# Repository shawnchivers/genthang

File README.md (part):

```
 ██████╗ ███████╗███╗   ██╗████████╗██╗  ██╗ █████╗ ███╗   ██╗ ██████╗ 
██╔════╝ ██╔════╝████╗  ██║╚══██╔══╝██║  ██║██╔══██╗████╗  ██║██╔════╝ 
██║  ███╗█████╗  ██╔██╗ ██║   ██║   ███████║███████║██╔██╗ ██║██║  ███╗
██║   ██║██╔══╝  ██║╚██╗██║   ██║   ██╔══██║██╔══██║██║╚██╗██║██║   ██║
╚██████╔╝███████╗██║ ╚████║   ██║   ██║  ██║██║  ██║██║ ╚████║╚██████╔╝
 ╚═════╝ ╚══════╝╚═╝  ╚═══╝   ╚═╝   ╚═╝  ╚═╝╚═╝  ╚═╝╚═╝  ╚═══╝ ╚═════╝ 
▀▀▀▀▀▀▀▀▀▀▀▀▀▀▀▀▀▀▀▀▀▀▀▀▀▀▀▀▀▀▀▀▀▀▀▀▀▀▀▀▀▀▀▀▀▀▀▀▀▀▀▀▀▀▀▀▀▀▀▀▀▀▀▀▀▀▀▀▀▀▀▀▀
      M E G A   D R I V E  /  G E N E S I S   ·   T A N G   N A N O   2 0 K
```

# Gen Thang

**Gen Thang is a DIY Sega Genesis / Mega Drive console project for the
[Sipeed Tang Nano 20K](https://wiki.sipeed.com/hardware/en/tang/Tang-Nano-20K/Nano-20K.html).**
A typical emulator recreates a console in software. Gen Thang does it in
hardware instead, using an FPGA chip configured to work like the original console.

Copy your own game ROMs to a microSD card (also called a TF card), choose a game
from the on-screen menu, and play. The standard build sends video and audio over
720p HDMI. You need a computer to program the board initially, but not to play.
Games are not included.

You can build it as a **TV console with Genesis controllers** or a **handheld
with built-in buttons and a small screen**. This repository contains the FPGA
design, menu firmware, build tools and optional PCB and printable-case designs.
You can use a [prebuilt release image](#choose-a-release-image) without compiling
the source yourself.

<p align="center">
  
</p>
<p align="center"><sub>Three-button handheld mock-up: Streets of Rage 2 frames from
Gen Thang's Verilator simulation composited onto a 3D render.
This is not footage from a physical handheld.
<a href="hardware/modern-3btn-handheld/index.html">Explore the handheld build guide.</a></sub></p>

> **Alpha software.** Gen Thang is under active development and is published as an
> early alpha. Expect bugs, game-compatibility gaps, missing features and breaking
> changes between releases. The default dual-DB9 build and raw-button variant are
> built and timing-checked but have not yet been tested on the new canonical wiring. The
> legacy single-DB9 breadboard image was tested by the author with a wired Genesis
> pad on its now-deprecated wiring, but only that one setup. Save
> states are experimental. Core switching rewrites the board's SPI flash. There is
> no warranty; you build, wire and flash at your own risk, and wiring mistakes can
> damage the board or a controller. See [Disclaimer](#disclaimer).

## Contents

**First build?** Start with [What you need](#what-you-need), then choose an
[assembly guide](#assembly-guides) for your controller or handheld arrangement.
The detailed pin tables and developer sections are references; you do not need
to read them all to understand the project.

- **See what it does:** [Features](#features) · [Game gallery](#game-gallery-streets-of-rage-2-sonic-2-and-x-men)
- **Build the hardware:** [Assembly guides](#assembly-guides) · [PCB and printable case](#pcb-and-printable-case) · [DB9 + biomech build guide](hardware/dual-db9-opt-pcb/index.html)
- **Set up the board:** [What you need](#what-you-need) · [Choose a release image](#choose-a-release-image) · [Flash](#1-flash-the-board) · [Prepare the card](#2-prepare-the-tf-card) · [Connect controllers](#3-connect-a-controller)
- **Play and use the menu:** [Using Gen Thang](#using-gen-thang) · [Controls](#controls) · [Options](#options-menu) · [Display options](#display-options) · [Save states](#save-states) · [USB upload](#uploading-roms-over-usb-serial) · [Core switching](#switching-cores)
- **Develop and debug:** [Build from source](#build-from-source) · [Simulation and screenshots](#simulation-and-screenshots) · [Limitations and troubleshooting](#limitations-and-troubleshooting)
- **About the project:** [Credits and tooling](#credits-and-tooling) · [Disclaimer](#disclaimer) · [License](#license)

## Features

- Motorola 68000 (fx68k), Z80 (T80), VDP, YM2612 (JT12) and SN76489 (JT89)
  implementations from the MiSTer Genesis core, running at 54 MHz and locked to
  the 60 Hz HDMI frame.
- 720p HDMI with audio. The picture is scaled to a centred 4:3 window.
- ROM browser on the TF card (`.md`, `.bin`, `.gen`, up to 4 MB) with an options
  page for resume, reset, save/load state and display settings.
- Controller options: two Genesis 3/6-button pads on DB9 breakouts (default), or
  twelve directly wired buttons for handhelds on the same physical GPIO layout.
- One save-state slot per game, with "Resume saved game" after a power cycle.
- Scanline and composite-blend display options.
- Optional ROM and core-image upload over the board's USB serial port (only in
  `GT_SERIAL_UPLOAD=1` builds; the default build leaves it out to fit the FPGA).

Not supported: SVP (Virtua Racing), EEPROM cartridges, Game Genie, interleaved
`.smd` ROMs and battery-backed cartridge saves (cartridge SRAM lives in SDRAM and is
only preserved inside a save state). Timing is fixed at NTSC / 60 Hz, as inherited
from MDTang.

## Game gallery: Streets of Rage 2, Sonic 2 and X-Men

Gen Thang's Genesis core playing the intro and attract mode (the unattended
demo) of three games, from ROMs you supply. These native 320x224 frames were
captured from Gen Thang running in its Verilator reference testbench (ideal memory;
see [Simulation and screenshots](#simulation-and-screenshots)). They are Gen Thang
simulation output, not captures from another emulator or from the physical HDMI port.

### Streets of Rage 2

<table>
  <tr>
    <td><br><sub>Boot logo</sub></td>
    <td><br><sub>Story intro</sub></td>
    <td><br><sub>The city</sub></td>
    <td><br><sub>Mr. X and the city</sub></td>
  </tr>
  <tr>
    <td><br><sub>Title screen</sub></td>
    <td><br><sub>Attract mode: Stage 1</sub></td>
    <td><br><sub>Attract mode: a fight</sub></td>
    <td><br><sub>High scores</sub></td>
  </tr>
</table>

### Sonic The Hedgehog 2

<table>
  <tr>
    <td><br><sub>Boot logo</sub></td>
    <td><br><sub>Title screen</sub></td>
    <td><br><sub>Chemical Plant Zone (demo)</sub></td>
  </tr>
  <tr>
    <td><br><sub>Chemical Plant Zone (demo)</sub></td>
    <td><br><sub>Aquatic Ruin Zone (demo)</sub></td>
    <td><br><sub>Aquatic Ruin Zone (demo)</sub></td>
  </tr>
</table>

### X-Men

<table>
  <tr>
    <td><br><sub>Boot logo</sub></td>
    <td><br><sub>Title screen</sub></td>
    <td><br><sub>Story text</sub></td>
    <td><br><sub>Demo: Cyclops</sub></td>
  </tr>
  <tr>
    <td><br><sub>Demo: Cyclops</sub></td>
    <td><br><sub>Demo: Cyclops</sub></td>
    <td><br><sub>Demo: Wolverine</sub></td>
    <td><br><sub>Demo: Wolverine</sub></td>
  </tr>
</table>

<sub>Frames produced by Gen Thang running in its Verilator reference testbench.
That testbench uses ideal memory and BRAM VRAM rather than the full board's SDRAM
controller and menu firmware; these are simulation captures, not physical HDMI
captures.</sub>

## Assembly guides

Start here for step-by-step hardware builds, including parts, printing, assembly
and firmware setup. Choose the guide and firmware that match your hardware.

| Build | Assembly guide | Firmware |
|---|---|---|
| Two-player DB9 console with biomechanical case | [Illustrated build guide](https://shawnchivers.github.io/genthang/hardware/dual-db9-opt-pcb/) · [Offline page](hardware/dual-db9-opt-pcb/index.html) | `db9` |
| Standalone L3 dual-DB9 carrier with stereo line-out | [Colorful build guide and capacitor chooser](https://shawnchivers.github.io/genthang/hardware/dual-db9-lineout-pcb/) · [Offline page](hardware/dual-db9-lineout-pcb/index.html) | [Official v1.9.3 DB9 image](https://github.com/shawnchivers/genthang/releases/download/v1.9.3/genthang_nano20k_db9_flash.bin) |
| GenThang Modern 3-button handheld (beta) | [Illustrated build guide](https://shawnchivers.github.io/genthang/hardware/modern-3btn-handheld/) · [Offline page](hardware/modern-3btn-handheld/index.html) | `raw` |

**DB9 bench references:** [O1 soldering and pre-power checks](hardware/dual-db9-opt-pcb/ASSEMBLY.md)
· [Biomechanical case printing and assembly](hardware/dual-db9-biomech-case/README.md)
· [L3 line-out assembly](hardware/dual-db9-lineout-pcb/ASSEMBLY.md)
· [L3 capacitor selection](hardware/dual-db9-lineout-pcb/index.html#caps).

## PCB and printable case

The [hardware directory](hardware/README.md) includes the
[O1 dual-DB9 carrier PCB](hardware/dual-db9-opt-pcb/README.md) for two Genesis
controllers and an original
[Giger-inspired biomechanical case](hardware/dual-db9-biomech-case/README.md)
for the carrier and Tang Nano 20K.

**Build the console:** the [DB9 + biomech assembly guide](https://shawnchivers.github.io/genthang/hardware/dual-db9-opt-pcb/)
([local page](hardware/dual-db9-opt-pcb/index.html)) walks through parts sourcing,
printing, soldering, continuity tests, flashing, two-player bring-up and fitting
the carrier into the biomechanical case. It includes CAD illustrations, direct
PCB/STL downloads and a printable bench copy. This O1 build uses HDMI audio, not
the separate line-out carrier.

- **PCB:** KiCad sources, fabrication ZIPs, BOM, assembly instructions and
  continuity-test tables.
- **Case:** printable [base STL](hardware/dual-db9-biomech-case/stl/case_base.stl)
  and [lid STL](hardware/dual-db9-biomech-case/stl/case_lid.stl), an editable
  [STEP model](hardware/dual-db9-biomech-case/dual-db9-biomech-case.step), and
  parametric CadQuery source. The case has been printed.

**Handheld (beta):** the [GenThang Modern 3-button build guide](https://shawnchivers.github.io/genthang/hardware/modern-3btn-handheld/)
([source](hardware/modern-3btn-handheld/index.html)) walks through printing and assembling a battery-powered A·B·C handheld
with a 3.5" IPS screen, with 3D renders, an interactive viewer, wiring diagrams and the three
[STLs](hardware/modern-3btn-handheld/stl/). It uses the `raw` firmware.

**Standalone stereo line-out:** the [L3 carrier](hardware/dual-db9-lineout-pcb/README.md)
adds a 3.5 mm output for powered speakers, with GPIO31 left and GPIO17 right.
Its [colorful build guide](https://shawnchivers.github.io/genthang/hardware/dual-db9-lineout-pcb/)
includes a simple capacitor chooser, soldering and electrical
checks. The author confirms the GPIO17 audio move works and has submitted L3 to
OSH Park. Use the [L3 order ZIP](hardware/dual-db9-lineout-pcb/dual-db9-lineout-L3-OSHPARK.zip)
and the [official v1.9.3 DB9 image](https://github.com/shawnchivers/genthang/releases/download/v1.9.3/genthang_nano20k_db9_flash.bin).
L3 is a separate carrier; it does not fit the O1 biomechanical case above.

**OSH Park is the recommended PCB manufacturer for people within the USA.** Use the [OSH Park order ZIP](hardware/dual-db9-opt-pcb/dual-db9-opt-O1-OSHPARK.zip).

The carrier uses the standard `db9` firmware and the pinout in
[step 3](#3-connect-a-controller). It is unprotected **3.3 V-only**. This worked
on my personal configuration, but not all third-party controllers might work; only
3-button and 6-button SEGA OEM controllers were tested.

## What you need

- Tang Nano 20K and a USB-C cable.
- microSD / TF card (FAT32 or exFAT) and your own Mega Drive ROM files.
- HDMI display (with audio, if you want sound).
- A controller arrangement from [step 3](#3-connect-a-controller).
- Gowin Programmer (part of Gowin EDA) to write the flash. The Education edition
  1.9.11.03 is what was used for the releases.

ROM images and other copyrighted game data are **not** included.

## Choose a release image

Each release contains a bitstream for every controller arrangement. Every
`*_flash.bin` is a complete SPI-flash image (bitstream at `0x000000`, menu
firmware at `0x500000`); the `.fs` files are bitstream-only.

| Image | Controllers | Notes |
|---|---|---|
| `genthang_nano20k_db9_flash.bin` | Two Genesis pads on DB9 breakouts (default) | Canonical J6/J5 wiring, 3.3 V only; see [dual Genesis pads](#dual-genesis-pads-db9-build) |
| `genthang_nano20k_raw_flash.bin` | Twelve direct buttons | Handheld pinout, plus the Nano's speaker and a headphone jack; see [direct buttons](#direct-buttons-raw-build) |
| `genthang_nano20k_raw_3btn_flash.bin` | Single-player three-button handheld | Raw pinout; port 2 reads as unplugged and **Mode** alone opens the menu |
| `genthang_nano20k_db9_800x480_flash.bin`, `genthang_nano20k_raw_800x480_flash.bin` | Same pads, for an 800x480 TFT on a TFP401 board | Native 800x480 DVI, no HDMI audio; see [display options](#display-options) |

The wiring must match the image you flash. A mismatched image reads the wrong pins.

## Setup

### 1. Flash the board

Write the `*_flash.bin` for your controller arrangement at SPI-flash address
`0x000000`. Verify it against the release's `SHA256SUMS` first
(`sha256sum -c SHA256SUMS --ignore-missing`).

**Gowin Programmer GUI (Windows or Linux):** connect the board, open *Gowin
Programmer*, choose series **GW2AR** and device **GW2AR-18C**, then double-click the
operation. Set *Access Mode* to **External Flash Mode** and *Operation* to **exFlash
Erase, Program thru GAO-bridge**, pick the `*_flash.bin` file (switch the file
filter to `*.*`), set *Start Address* to `0x000000` and run it. The
[SNESTang installation guide](https://github.com/nand2mario/snestang/blob/main/doc/installation.md)
has screenshots of the same dialogs.

**Linux, command line:** the on-board BL616 debugger claims the FTDI interface;
release it first (repeat after every replug), then use the programmer. In our
testing openFPGALoader did not work with this board's debugger.

```sh
echo -n 1-2:1.0 | sudo tee /sys/bus/usb/drivers/ftdi_sio/unbind   # adjust 1-2 to your USB port
cd "$GOWIN_HOME/Programmer/bin"      # your Gowin EDA install directory
QT_QPA_PLATFORM=minimal ./programmer_cli --device GW2AR-18C --run 39 \
    --mcuFile /path/to/genthang_nano20k_db9_flash.bin --spiaddr 0x000000
```

A `.fs` file can be loaded into SRAM for a quick test, but it does not include the
menu firmware, so a flash image is required for normal use.

### 2. Prepare the TF card

Format the card with an MBR partition table and a FAT32 (or exFAT) filesystem, then
copy your `.md`, `.bin` or `.gen` ROMs onto it, in folders if you like. On Linux:

```sh
sudo parted /dev/sdX --script mklabel msdos mkpart primary fat32 1MiB 100%
sudo mkfs.vfat -F 32 -n GENTHANG /dev/sdX1
```

(Replace `/dev/sdX` with your card and double-check it first: this erases the card.)
Insert the card, connect HDMI and a controller, then power the board. To add ROMs
later, copy them to the card in a normal card reader. (Builds made with
`GT_SERIAL_UPLOAD=1` can also copy them over USB; see
[Uploading ROMs over USB serial](#uploading-roms-over-usb-serial).)

### 3. Connect a controller

Always **power the board off before wiring** controllers. The FPGA pins are 3.3 V
only and are not 5 V tolerant. In the tables below, the "FPGA pin" is the GPIO
number used in the constraints file; the "Nano contact" is the header position,
counted 1-20 from the USB-C end with the board viewed from above (USB at the top):
**J6** is the left header and **J5** the right header.

The original single-DB9 breadboard layout is documented separately in
[deprecated controller pinouts](docs/deprecated-pinouts.md). It is not included
in current releases.

#### Dual Genesis pads (`db9` build)

For a PCB instead of hand wiring, see the
[dual-DB9 carrier and matching printable case](#pcb-and-printable-case).

For two wired 3- or 6-button Genesis pads, use
`genthang_nano20k_db9_flash.bin`. Player 1 is entirely on J6 and player 2 entirely on J5.
Leave the Nano LCD connector and speaker header empty. Both ports use 3.3 V with
internal pull-ups; the DB9 pin 5 supply is 3.3 V.

| DB9 pin (male) | Signal | Player 1 FPGA pin (contact) | Player 2 FPGA pin (contact) |
|---|---|---|---|
| 1 | Up / D0 | 73 (J6.1) | 42 (J5.5) |
| 2 | Down / D1 | 74 (J6.2) | 41 (J5.6) |
| 3 | Left / D2 | 77 (J6.5) | 51 (J5.9) |
| 4 | Right / D3 | 27 (J6.8) | 48 (J5.10) |
| 5 | Pad supply | **3.3 V, not 5 V** (J6.19) | **3.3 V, not 5 V** (J5.16) |
| 6 | TL (B / A) | 28 (J6.9) | 49 (J5.12) |
| 7 | TH select (output) | 29 (J6.12) | 72 (J5.17) |
| 8 | Ground | GND (J6.20) | GND (J5.15) |
| 9 | TR (C / Start) | 30 (J6.13) | 71 (J5.18) |

##### P1 breadboard wiring

P1 can be built on a 30-row breadboard using only J6. Seat the Nano
component-side up with USB-C at the top, put J6.1 in hole `b5`, and connect a
passive **male DB9 screw-terminal or solder-cup breakout** with nine jumpers:

| DB9 pin | Function | Breakout jumper | Nano hole | Nano contact |
|---:|---|---|---|---|
| 1 | Up / D0 | terminal 1 to `a5` | `b5` | J6.1, GPIO73 |
| 2 | Down / D1 | terminal 2 to `a6` | `b6` | J6.2, GPIO74 |
| 3 | Left / D2 | terminal 3 to `a9` | `b9` | J6.5, GPIO77 |
| 4 | Right / D3 | terminal 4 to `a12` | `b12` | J6.8, GPIO27 |
| 5 | Controller supply | terminal 5 to `a23` | `b23` | J6.19, **3.3 V only** |
| 6 | TL / B, A | terminal 6 to `a13` | `b13` | J6.9, GPIO28 |
| 7 | TH select | terminal 7 to `a16` | `b16` | J6.12, GPIO29 |
| 8 | Ground | terminal 8 to `a24` | `b24` | J6.20, GND |
| 9 | TR / C, Start | terminal 9 to `a17` | `b17` | J6.13, GPIO30 |

A bare DB9 does not fit a 2.54 mm breadboard. Check the numbered terminals and
your breadboard's internal row connections with a continuity meter before
connecting the Nano. DB9 pin 5 is **3.3 V only, never 5 V**; power off before
wiring or connecting a controller, and do not hot-plug this unprotected setup.
An optional 100 nF ceramic capacitor may be fitted directly across DB9 pins 5
and 8. Use the normal `genthang_nano20k_db9_flash.bin`; P2 may remain
disconnected.

Build it with:

```sh
GT_PAD=db9 ./build.sh
```

#### Direct buttons (`raw` build)

For handheld builds: twelve buttons, each switching an FPGA pin to GND (the
internal pull-ups are enabled), plus the Nano's speaker and a headphone jack (see
[speaker and headphone jack](#speaker-and-headphone-jack-raw-build)).

The pinout is laid out for a Nano mounted component side forward with USB-C at the
top. The left header (J6) faces the D-pad and the jack, and the right header (J5)
faces the face buttons. Groups sit on neighbouring pins, for neat solder runs or
multi-pin Dupont housings.

| Header pin | FPGA pin | Function | | Header pin | FPGA pin | Function |
|---|---|---|---|---|---|---|
| J6.8 | 27 | Up | | J5.3 | 76 | Start |
| J6.9 | 28 | Down | | J5.5 | 42 | X |
| J6.10 | 25 | Left | | J5.6 | 41 | A |
| J6.11 | 26 | Right | | J5.10 | 48 | Y |
| J6.12 | 29 | Headphone detect | | J5.12 | 49 | B |
| J6.13 | 30 | Jack R | | J5.13 | 86 | Mode |
| J6.14 | 31 | Jack L | | J5.17 | 72 | Z |
| J6.20 | GND | Button and jack ground | | J5.18 | 71 | C |
| | | | | J5.15 | GND | Button ground |

- Each face-button column shares neighbouring pins: X/A on J5.5–6, Y/B on
  J5.10/12 and Z/C on J5.17–18.
- The pins skipped on J5 belong to the TF card (80), the speaker amplifier (51,
  54–56) and the LED strip (79).
- Spare: 73, 74, 75 and 77 (J6.1, J6.2, J6.3, J6.5).
- In vector order, `btn_n[0..11]` (`B, A, Mode, Start, Up, Down, Left, Right, C, Y,
  X, Z`) uses pins `49, 41, 86, 76, 27, 28, 25, 26, 71, 48, 42, 72`.
- Releases up to 1.6.2 used the DB9 data pins for the raw build instead
  (`73, 74, 77, 27, 28, 30, 42, 41, 51, 48, 49, 71`). Rewire older raw builds when
  updating.

## Using Gen Thang

At power-on the menu lists the card's folders and ROMs sorted by name. If the card
cannot be read the status line says why (no reply, not initialised, not FAT32 /
exFAT). Picking a ROM streams it into SDRAM (about 7 s for 2 MB) and starts the game.

<p align="center"><sub>Menu overlay rendered by the Verilator testbench (see
<a href="#simulation-and-screenshots">Simulation and screenshots</a>).</sub></p>

### Controls

Everything in the menus needs only the D-pad, A/B/C and Start, so a 3-button pad
is enough. Player 1 drives the menu; player 2 only plays.

| Genesis control | Games page | Options page | In game |
|---|---|---|---|
| D-pad | move; Left/Right = page | move; Left/Right = change value | D-pad |
| A | parent folder | back to games (no game loaded) | A |
| B / C | open folder / load ROM | select | B / C |
| X / Y / Z | - | - | X / Y / Z |
| Start | open Options | resume the game | Start |
| Start+A+B+C or Mode+Start | resume the game | resume the game | open the menu (the game pauses) |

### Options menu

The Options page opens first when you call up the menu during a game:

- **Resume game**, **Save state**, **Load state**, **Reset game**, **Load another game**
- **Scanlines**: off, 25 %, 50 %
- **Composite blend**: off, on
- **Video output**: HDMI, or DVI with audio on the line-out jack only (see [display options](#display-options))
- **Display**: TV (default), or 4:3 LCD
- **Brightness**: 100 % (default), 75 %, 50 %, 25 % (raw build only)

The running firmware version is shown below the **GEN THANG** title on every menu page.

Opening the menu pauses the game and mutes HDMI audio. **Reset game** pulses the
console reset input without clearing work RAM, like the physical Genesis reset
button (this is the reset X-Men's Mojo level expects). Display settings are saved
to `GENTHANG.CFG` on the card. Scanlines and composite blend never affect the menu
itself, nor does brightness; video output and display apply to the menu too.

### Display options

The menu draws at 256x224 and the game at 320x224 or 256x224, both scaled into the
same centred 960x720 (4:3) window inside the 1280x720 HDMI frame by default. Two
post-processing options are applied by the HDMI scaler:

- **Scanlines** dims the lower half of each Genesis line by 25 % or 50 %. It is
  skipped in interlaced modes.
- **Composite blend** averages each pixel with its left neighbour, which melts the
  dither patterns many games use for transparency and shading the way a composite
  cable does. Version 1.9.3 removes adaptive blending to make room for the YM2612
  ladder effect; a saved adaptive setting becomes normal blend ON. Custom builds
  can restore adaptive with `GT_NO_ADAPTIVE=0`, subject to FPGA fit and timing.

**Brightness** exists only in builds with `GT_PICTURE=1`, the default for the raw
(handheld) build; the DB9 build leaves it out because the FPGA has no logic to spare,
and its menu does not show it. It dims the game picture to 75 %, 50 % or 25 % using the
scanline dimmer: on scanline rows the scanline and brightness levels add, down to 25 %.
On handheld (`GT_PICTURE=1`) builds the menu is always drawn at a fixed 50 % so it is
not harsh on the LCD; Brightness does not change it. This is software dimming, not LCD backlight control:
it does not reduce backlight power or improve the panel's black level, and dark detail
can be lost. The setting is saved to `GENTHANG.CFG` and kept, unused, when the card
moves to a DB9 board. (1.9.0 also had a Color mode; it was removed in 1.9.1 because that
picture stage broke audio and game loading on the handheld.)

**Video output** chooses HDMI (default, with audio) or DVI. DVI sends the same
720p60 picture without HDMI data islands, so the display gets no audio; use the
[line-out jack](#line-out-jack-db9-and-raw-builds) for sound. Use it if a
display pulses or flickers on mid and dark tones: on an LG 50PN6500 plasma, any HDMI
data island made the picture pulse regardless of its contents, and DVI was stable.

**Display** chooses **TV** (default, the centred 4:3 window) or **4:3 LCD**.
Use LCD mode for a 640x480 panel/controller such as the PCB800850 that squeezes
the entire 1280x720 input onto its 4:3 panel. It expands the game and menu across
the full input width (the leftmost 3 pixels stay black), removing the built-in side bars so the controller's
downscaling restores the intended proportions. On a normal 16:9 TV this mode
looks stretched; switch back to TV there. HDMI timing stays at 720p60, and no
extra framebuffer is used. Changes take effect at a frame boundary and are
saved to `GENTHANG.CFG`; settings from older versions still load with TV mode.

**Bare TFT panels behind a DVI/HDMI decoder board** (such as the Adafruit TFP401
with an 800x480 40-pin TFT) have no scaler, so they cannot show 720p at all. Build
the `GT_VIDEO=800x480` variant (`genthang_nano20k_<pad>_800x480.fs`) for them. It
outputs native 800x480 at 59.9 Hz (CVT timing, 29.7 MHz pixel clock), always as DVI
because the TFP401 cannot receive audio, so use the line-out jack for sound. TV mode
shows a centred 640x480 4:3 window; 4:3 LCD mode fills the full 800 width.

<p align="center"><sub>The same spotlight scene with composite blending off, on
and adaptive in earlier releases, cropped to show how each mode affects the light, character and floor
dither.</sub></p>

### Save states

Save states are **experimental**. There is one slot per game, stored next to the ROM
as `<rom name>.ss0` (about 200 KB). **Save state** and **Load state** from the
Options page return you to the game. The last ROM path is stored in `GENTHANG.CFG`,
so after a power cycle the start-up options offer **Resume saved game**, which
reloads that ROM and restores its state.

How it works: the menu parks the 68000 in a small routine
([firmware/m68k/savestate.s](firmware/m68k/savestate.s)) through a level-7
interrupt, freezes the Z80 at an instruction boundary, and saves work RAM, VRAM,
CRAM, VSRAM, VDP registers, Z80 RAM and registers, YM2612 registers, I/O and
cartridge SRAM. **Not saved:** PSG and YM2612 key-on state (notes resume at the next
key-on), the VDP FIFO and the raster position. A state only fits the exact ROM it was
made from.

### Uploading ROMs over USB serial

**Not in the default build or releases.** The serial UART is only built with
`GT_SERIAL_UPLOAD=1 ./build.sh`. Its fit is not certified with the 1.9.3 ladder
configuration; the default DB9 build already has very little logic headroom.
Without it the menu ignores the serial port; copy ROMs and core images to the card in
a card reader instead.

`genthang-upload` copies ROMs or core images to the inserted TF card through the Nano
20K's USB serial port. The card stays FAT32 / exFAT and still works in a normal
reader.

```sh
./upload/genthang-upload /dev/ttyUSB0 game.md
./upload/genthang-upload /dev/ttyUSB0 game.md --name "Game Name.md"
./upload/genthang-upload-gui.py     # GTK 3 frontend (needs the GTK 3 Python bindings)
```

The GUI detects the Sipeed debugger, accepts files by picker or drag and drop, and
shows progress and device errors. The transfer is CRC32-verified before it replaces
the destination, so an interrupted upload leaves the previous file intact. **Leave
the on-screen menu open during the transfer**: the PicoRV32 is stalled while a game
runs and cannot receive anything. The tool defaults to 460800 baud because the
debugger's USB-UART runs at four times the FPGA's setting; use `--baud 115200` with
corrected debugger firmware. On Linux your user needs access to the serial device
(usually the `dialout` group).

### Switching cores

Official 1.9.3 builds use `GT_NO_CORE_SWITCH=1`, which removes the runtime flash
interface and hides this menu entry to make room for ladder audio.
It also rejects serial core-image uploads; normal ROM loading and firmware bootstrap
from flash are unchanged. The FPGA reports this omission in core-ID bit 20 and the
adaptive omission in bit 19, so use the matching menu firmware from this worktree.

Custom builds with `GT_NO_CORE_SWITCH=0` can restore this feature, subject to FPGA
fit and timing. In those builds, *Switch core* lists complete SPI-flash images (`.bin`) in `/cores`, programs the one
you pick into the board's flash and asks you to power-cycle. Copy one to `/cores` on
the card (or, in a `GT_SERIAL_UPLOAD=1` build, upload it with
`./upload/genthang-upload /dev/ttyUSB0 other_flash.bin --core`). It must be up to 8 MB, a full flash
image, not a Gowin `.fs`; Gen Thang's own `*_flash.bin` files qualify. **Do not
remove power while the menu says `FLASHING`.** An interrupted write may need
recovery with Gowin Programmer over USB.

## Build from source

### Toolchain

- **Gowin EDA** Education 1.9.11.03 or a compatible release (`gw_sh`). Set
  `GOWIN_HOME` to its install directory (or `GW_SH` to the `gw_sh` binary, or put
  `gw_sh` on `PATH`); `build.sh` then sets the software rendering and FreeType
  environment the tools need on Linux. No install location is assumed. The IDE
  project uses SystemVerilog 2017.
- Only to change the menu: a RISC-V GCC (`riscv64-unknown-elf`, with picolibc) and
  m68k binutils. `firmware/firmware.bin` and `firmware/ss_stub.h` are committed and
  were checked to rebuild bit-for-bit with GCC 13.2 / binutils 2.42.
- Only for simulation: Verilator 5, `mtools` and `mkfs.vfat`.

```sh
git clone https://github.com/shawnchivers/genthang.git
cd genthang
./build.sh                        # impl/pnr/genthang_nano20k_db9.fs, dual DB9 build
GT_LADDER=0 ./build.sh            # custom clean-output audio build
GT_PAD=raw ./build.sh             # twelve direct buttons + Nano speaker (handheld pinout)
GT_VIDEO=800x480 ./build.sh       # native 800x480 DVI for a bare TFT on a TFP401 board
GT_PAD=raw GT_3BTN=1 ./build.sh   # 3-button handheld (*_3btn): no player 2, Mode alone opens the menu
GT_PICTURE=0 GT_PAD=raw ./build.sh  # raw build without the brightness option
./release.sh                      # all variants (db9, raw, raw_3btn, *_800x480) + flash images + tarball
```

`GT_PAD` (`db9`, `raw`) selects the supported pad ports in `src/mdtang_top.sv`, through
`src/pad_config.vh` (written by `build.tcl`) and `src/boards/nano20k_<pad>.cst`.
The raw build has its own handheld pinout; DB9 uses 12 data GPIOs and two TH outputs. The old `GT_PINOUT=breadboard` and `breadboard-rev1` values are deprecated
aliases for canonical DB9 and print a warning. The DualShock (`GT_PAD=ds`) build has
been removed.
`GT_3BTN=1` is for the single-player three-button handheld: player 1 reads as a 3-button
pad (Mode, X, Y and Z are not passed to games), port 2 reads as unplugged, and Mode alone
(held 20 ms) opens the menu instead of Mode+Start. The firmware reads it from bit 18 of
the core ID register. Output names get a `_3btn` suffix.
`GT_SERIAL_UPLOAD=1` adds the iosys UART for USB serial uploads. It is off by default
to leave logic headroom; its fit is not certified for 1.9.3. `GT_PICTURE`
(`0`/`1`) adds the brightness option to the HDMI scaler; it defaults to
`1` for `GT_PAD=raw` and `0` for DB9, which cannot fit it. The firmware reads the choice
from bit 16 of the core ID register, so one `firmware.bin` serves both. The default build also runs
the menu's PicoRV32 with a single-read-port register file, which halves its
distributed RAM at the cost of a slightly slower menu CPU.
The 1.9.3 defaults are `GT_LADDER=1`, `GT_NO_ADAPTIVE=1` and `GT_NO_CORE_SWITCH=1`.
JT12's YM2612 Model 1 DAC ladder distortion is enabled, while adaptive blending and
runtime core switching are omitted. Normal blend OFF/ON and scanlines remain.
Each flag accepts `0` or `1` for custom builds; changing the feature set requires a
fresh placement and timing check. `release.sh` explicitly fixes the official
feature set for every variant regardless of caller environment.
The earlier GPIO17/L3 ladder experiment with adaptive and core switching retained
did not fit the Nano 20K. The initial
build left 218 equivalent LUTs unplaced. Sharing a 10-bit ladder sum between the
stereo outputs reduced that to 100, but both timing-priority and balanced placement
still exhausted all 10,368 CLS. No ladder-enabled bitstream was generated.
The arithmetic optimization passes `tests/jt12_ladder_tb.sv`, which checks all
4,096 accumulator/panning/ladder combinations against the original output equations,
including clock-enable holds. Those full-featured attempts could not proceed to
hardware testing because placement failed.
The trimmed experiment removes only adaptive blending and core switching. It
keeps normal blend OFF/ON, scanlines, game loading, reset and save states. It also
sizes the flash-bootstrap counter to the firmware length; the flash test checks
both 4-byte and full 256 KiB loads, with and without runtime flash access.

**Historical 1.9.2 GPIO17/L3 ladder prerelease:** placement and routing pass, with
20,608/20,736 logic slots and 10,359/10,368 CLS used (128 logic slots and 9 CLS spare).
`clk_sys` reaches 63.534 MHz, `clk_z80` 44.117 MHz and `hclk` 76.879 MHz; all exceed
their targets, with zero negative setup/hold slack.
- [Combined flash image with matching menu firmware](builds/db9-gpio17-ladder-trimmed/genthang_nano20k_db9_gpio17_ladder_trimmed_flash.bin):
  program at SPI-flash address 0. GPIO31 left audio, GPIO17 right audio and both
  DB9 controller pinouts are unchanged.
- [SRAM bitstream](builds/db9-gpio17-ladder-trimmed/genthang_nano20k_db9_gpio17_ladder_trimmed.fs):
  use only after the matching menu firmware is installed in SPI flash. The older
  GPIO17 menu does not know that adaptive and core switching are disabled.
- [Checksums](builds/db9-gpio17-ladder-trimmed/SHA256SUMS) and
  [build configuration, source hashes and validation results](builds/db9-gpio17-ladder-trimmed/build-info.json).

This pre-release image was flashed, verified and tested on hardware; the user
confirmed working operation and audio closer to the original. Its menu version
remains 1.9.2; identify it by the `gpio17_ladder_trimmed` filenames.
Gowin runs share intermediate files
in `impl/`, so do not run two builds concurrently in one checkout.

Gowin writes `impl/pnr/genthang_nano20k.bin` (bitstream) and `.fs`. Combine the
bitstream with the menu firmware into a flash image yourself with:

```sh
python3 merge_flash.py impl/pnr/genthang_nano20k.bin firmware/firmware.bin genthang_nano20k_flash.bin
```

`release.sh` does this for each variant and refuses to package a build that misses
the `clk_sys`, `clk_z80` or `hclk` targets or leaves negative setup/hold slack. The
design nearly fills the FPGA (see [Resource use](#resource-use)), so even small RTL
changes can break timing. Rebuild the menu with:

```sh
cd firmware
make RISCV=/usr/bin/riscv64-unknown-elf EXTRA_CFLAGS="-isystem /usr/lib/picolibc/riscv64-unknown-elf/include"
```

The internal module and file names (`mdtang_top`, `md20k_core`, `sdram_md20k`) keep
the project's MDTang lineage and are intentionally not renamed.

### Resource use

The design nearly fills the Nano 20K's FPGA. Release builds use timing-priority
placement and timing-directed routing. Post-route timing for this release has zero
negative setup and hold slack:

| Variant | `clk_sys` Fmax (needs 54.0 MHz) | `clk_z80` Fmax (needs 27.0 MHz) | `hclk` Fmax (720p needs 74.25 MHz; 800x480 needs 29.7 MHz) |
|---|---|---|---|
| `db9` | 63.534 MHz | 44.117 MHz | 76.879 MHz |
| `raw` | 57.783 MHz | 50.044 MHz | 82.740 MHz |
| `raw_3btn` | 62.023 MHz | 47.732 MHz | 80.840 MHz |
| `db9_800x480` | 65.307 MHz | 46.219 MHz | 71.688 MHz |
| `raw_800x480` | 63.952 MHz | 45.457 MHz | 82.323 MHz |

Every release build is rejected if a clock misses its target or the timing report
contains negative setup or hold slack.

## Simulation and screenshots

The Gen Thang Verilator testbenches in [verilator/](verilator) run the synthesisable
core with the real menu firmware against models of the SDRAM, SPI flash and TF card
(`make dut`), and the same Gen Thang Genesis core in a faster reference configuration
with ideal memory and BRAM VRAM but no menu, SDRAM controller or firmware (`make ref`).
The full-board configuration is too slow to reach the attract modes (see below), so
the game frames in this README come from Gen Thang's reference testbench; the menu
images (`menu-*.png`) come from its full-board testbench.

```sh
cd verilator
make dut ROM=/path/to/game.md              # whole board core + firmware + FAT32 card image
make run-dut ARGS="-T 1700 -O 900"         # boot the menu and dump the overlay (run/dut/overlay_900.ppm)
make textdisp                              # the menu overlay alone -> run/textdisp/*.ppm
make genesis-pad gen-io                    # unit tests for the DB9 pad reader and the I/O block
make picture-modes picture-settings        # RGB pipeline and saved/menu picture settings (no ROM needed)
make ref ROM=/path/to/game.md && make run-ref ARGS="-n 300 -d 100,200"   # golden model
```

`make` needs `mcopy` and `mkfs.vfat`; set `MTOOLS=/dir/containing/mtools/` if `mcopy`
is not on `PATH`. `-t ms:len:mask` presses buttons at an absolute time and
`-p frame:len:mask` relative to the game start (mask bits 0-7: Right, Left, Down,
Up, A, B, C, Start; 8 Mode, 9 X, 10 Z, 11 Y; Mode+Start is `0x180`). `-d` dumps
frames as PPM, `-O` dumps the menu overlay. The simulation is slow (the whole board
runs at roughly 0.4 simulated seconds per minute), so a full ROM load takes tens of
minutes.

[verilator/hdmi_preview.py](verilator/hdmi_preview.py) converts a dumped frame or
overlay into a PNG as the HDMI scaler would show it (`--overlay`, `--scanlines`,
`--blend`, `--crop`). The images in [docs/images](docs/images) were produced this
way. Unit tests for the build selection and pin contract run with
`python3 -m unittest discover -s tests` (needs `tclsh`).

Results for this release: the full-board testbench booted the real menu firmware from
the SPI-flash model, initialised and mounted a FAT32 card model, loaded a 2.2 MB ROM
(560,691 ROM words written to SDRAM and checked against the file, none wrong; 4,422
card blocks read), started the game after 7.3 simulated seconds, and opened the menu
with Mode+Start during play, with zero SDRAM, flash and TF-card protocol errors.
The DB9 pad reader and the two-port I/O block unit tests pass, as do the four build
and pin-selection tests. The testbench does not exercise the HDMI frame lock, and
frame-by-frame equivalence of the whole board against the reference configuration
was not re-run for this release. The gallery therefore shows Gen Thang's Verilator
core output, not captures from the physical board's HDMI port. Hardware performance investigation notes are in
[docs/slowdown-test.md](docs/slowdown-test.md).

## Limitations and troubleshooting

- Alpha quality: compatibility is not exhaustive and timing is tight. Please report
  games that fail along with the image variant and ROM name.
- ROMs must be raw (not interleaved `.smd`), no larger than 4 MB, and use `.md`,
  `.bin` or `.gen`. No battery-backed saves are written; use save states.
- Save states are experimental and tied to the exact ROM; PSG phase, YM2612 key-on
  state, VDP FIFO contents and raster position are not restored.
- If the menu says the card is not FAT32/exFAT, reformat it with an MBR partition
  table and a FAT32 filesystem.
- USB upload is not in the default build (only with `GT_SERIAL_UPLOAD=1`, which has
  little logic headroom); where present it needs the on-screen menu open and serial
  access on your computer.
- Core switching rewrites the SPI flash; never interrupt power while it says
  `FLASHING`.
- Some Genesis pads need 5 V power and a 3.3 V level shifter, which the breadboard
  wiring does not provide; the FPGA inputs are not 5 V tolerant.
- No picture or menu: check the HDMI cable and display (the output is 720p60), that
  the flash image matches your hardware, and that the TF card is fully inserted.
- Picture pulses or flickers on a plasma TV (black and full white stay steady): set
  **Video output** to DVI in the options menu. The TV then gets no audio; use the
  line-out jack below for sound.

### Line-out jack (DB9 and raw builds)

A stereo 3.5 mm line-out is available on two otherwise unused header pins, in both HDMI
and DVI modes: left on FPGA pin 31 (J6 contact 14), right on pin 17 (J6 contact 15), ground on
J6 row 20 or J5 row 15. The raw build uses its own jack pins; see
[below](#speaker-and-headphone-jack-raw-build). The pins carry 1-bit (sigma-delta) audio, so each needs a small
filter:

```
pin ──1 kΩ──┬──10 µF (+ toward the resistor)──► jack tip (L) / ring (R)
          10 nF
GND ────────┴─────────────────────────────────► jack sleeve
```

The output is roughly 1 V peak to peak, for powered speakers, a soundbar or an amplifier;
it is not meant to drive headphones directly.

**Not hot-pluggable without the filter.** Wired straight to the pins (no resistor or
capacitors) the line-out works for a quick test, but plugging or unplugging the jack or
the speaker while the board is powered gave trouble. Power the board off first, or fit
the 1 kΩ / 10 nF / 10 µF filter, which isolates the pins. GPIO17 is unused by the controller
ports, but drives the Nano's on-board LED2 through a 510 Ω resistor; the LED can glow
with the audio. Unlike the old GPIO56 output, it is not a configuration pin or an
on-board amplifier input. Keep the Nano's speaker and LCD connectors empty.

**Carrier compatibility:** these DB9 builds use the
[L3 line-out carrier](https://github.com/shawnchivers/genthang-hw/tree/main/dual-db9-lineout-pcb)
pinout. Released images through 1.9.2 and L1/L2 carriers use GPIO56 (J5 contact 7)
for right audio. On an older carrier, use an isolated jumper from **Tang J6.15
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
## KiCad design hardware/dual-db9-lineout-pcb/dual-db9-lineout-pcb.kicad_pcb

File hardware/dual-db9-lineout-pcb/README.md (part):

# Two-player Genesis carrier with line-out — L3

**Start building:** the [illustrated L3 assembly guide](index.html) includes a
simple capacitor chooser, soldering steps, pre-power checks and firmware downloads.

**[O1](../dual-db9-opt-pcb/README.md) plus a stereo 3.5 mm line-out**, all through-hole for easy
DIY soldering. Same Nano socket parts, the same two DB9 ports and the same canonical
`GT_PAD=db9` pinout as O1, so player wiring and controllers are unchanged. The line-out
works in both HDMI and DVI modes, so a TV that flickers with HDMI data islands can run
in **Video output: DVI+LINE OUT** and get sound from powered speakers.

L3 keeps L2's Tang orientation on its top-mounted female headers: **USB-C power
left, HDMI right, audio at the rear, DB9 ports at the front**. No separate power
connector is added; the existing Tang USB-C port remains the power input.

**L3 changes only the right-audio connection:** GPIO17 at **J6 contact 15** now
feeds R2, instead of GPIO56 at J5 contact 7. Both DB9 player pinouts, left audio,
filter parts, dimensions and connector locations are unchanged. The Tang plugs
directly into L3 with no audio jumper; J5 contact 7 is unconnected on this carrier.
GPIO17 is unused by the controller ports but has the Nano's on-board LED2 load
(510 Ω to the LED supply). No LED modification is required for the selected pin
test; this revision does not guarantee noise-free audio.

## Reorder from OSH Park

Upload **[dual-db9-lineout-L3-OSHPARK.zip](dual-db9-lineout-L3-OSHPARK.zip)** to
[OSH Park](https://oshpark.com/) using its standard
[two-layer, 1 oz, 1.6 mm service](https://docs.oshpark.com/services/two-layer/).
Do not reorder from an L1/L2 ZIP. This package contains only the two copper,
two mask, two silkscreen, outline, plated-drill and non-plated-drill files.
Confirm the preview shows **100 × 70 mm**, two copper layers, the rear jack notch
and **three 0.60 × 1.40 mm plated jack slots** before paying. Check the L3
marking on the silkscreen. The author confirms successful testing of the GPIO17
right-audio move and has submitted L3 to OSH Park. See the
[test status](TEST-STATUS.md) for the scope of that confirmation; this remains a
prototype fabrication package, not a production qualification.

Verify the files with `sha256sum -c SHA256SUMS` from this directory. The
[validation report](validation.json) covers the firmware pin contract,
schematic/PCB equivalence, connector clearance, drill and annular-ring limits,
and DRC. Same board outline and mount/connector positions as L2, so its cases
remain mechanically compatible.

## Parts (every part is through-hole)

| Ref | Qty | Part | Notes |
|---|---:|---|---|
| J5, J6 | 2 | Harwin M20-7822046, 1×20 female socket, 2.54 mm, 8.5 mm tall | any similar 1×20 female header fits |
| J1, J2 | 2 | Kycon K22X-E9P-N, right-angle male DB9 | other DB9 parts are not fit-checked |
| J3 | 1 | CUI / Same Sky SJ1-3523N, 3.5 mm stereo jack, right angle | footprint is for this part |
| R1, R2 | 2 | 1 kΩ, ¼ W axial, 7.62 mm (0.3 in) pitch | |
| R3, R4 | 2 | 47 kΩ, ¼ W axial, 7.62 mm pitch | 22k–100k is fine |
| C1, C2 | 2 | 10 nF (code 103) ceramic disc or film, 5.0 mm pitch | |
| C3, C4 | 2 | 10 µF 16 V+ radial electrolytic, 5 mm dia, 2.0 mm pitch | **polarized** |

Full list with descriptions: [BOM.csv](BOM.csv).

## Line-out circuit (one per channel)

```
Nano pin ──R1/R2 1k──┬──C3/C4 10µF (+ toward R)──┬──► jack tip (L) / ring (R)
                     │                           │
                  C1/C2 10nF                 R3/R4 47k
                     │                           │
GND ─────────────────┴───────────────────────────┴──► jack sleeve
```

| Channel | FPGA pin | Nano contact | Jack |
|---|---|---|---|
| Left | GPIO31 (`audio_jack_l`) | J6.14 | tip, J3 pin 2 |
| Right | GPIO17 (`audio_jack_r`) | J6.15 | ring, J3 pin 3 |
| Ground | GND | J6.20 / J5.15 | sleeve, J3 pin 1 |

The 1 kΩ and 10 nF turn GenThang's 1-bit audio into an analog signal (≈16 kHz
corner). The 10 µF blocks the 1.65 V DC level. R3/R4 are extra compared with the
README breadboard filter: they keep the output side of the capacitor at 0 V so plugging
in a speaker does not give a loud pop. Output is about 1 V peak to peak: **powered
speakers, a soundbar or an amplifier, not headphones**.

### Optional Model 1-style low-pass filter

For a darker, original Genesis Model 1-style frequency response, replace **only C1
and C2**, one per channel. Keep R1/R2 at 1 kΩ:

| Filter option | C1 and C2 | Capacitor marking | Nominal cutoff |
|---|---|---|---|
| Stock L3 | 10 nF | `103` | 15.9 kHz |
| Model 1 VA0–VA2-style | 47 nF | `473` | 3.39 kHz |
| Model 1 VA3–VA6-style | 56 nF | `563` | 2.84 kHz |

**Simple choice:** start with two **10 nF (`103`)** capacitors for the stock
response. Choose **47 nF (`473`)** for a darker VA0–VA2-style response, or
**56 nF (`563`)** for a darker VA3–VA6-style response.
For the 56 nF option, use two film capacitors, 5% tolerance, 50 V,
5.0 mm lead spacing. These are nonpolarized; either direction works. Check the
chosen capacitor's body dimensions against the board and enclosure before buying.
Use the same value in both channels. Power off and unplug USB before replacing parts.

Leave R3/R4 at 47 kΩ and C3/C4 at 10 µF. The electrolytics remain polarized, with
their positive leads toward R1/R2, not the jack. No PCB trace or firmware changes
are required. The BOM, schematic and fabrication files retain the stock 10 nF value;
these substitutions are optional assembly variants.

The nominal corners use `fc = 1 / (2 * pi * R * C)`. R3/R4 and the connected
amplifier input load the filter, shifting the actual corner and output level; use a
high-impedance line input. These values approximate the analog low-pass cutoff,
not the complete sound of an original console's DAC, mixer and amplifier, or any
filtering already applied in firmware. This optional response has not been
hardware-measured on L3.

The revision-specific targets (3.39 kHz for VA0–VA2 and 2.84 kHz for VA3–VA6) are
described in [Genesis & Sega CD - Audio Filtering](https://jsgroth.dev/blog/posts/genesis-sega-cd-audio-filtering/#in-genesis-hardware).
This recommendation does not cover the different Model 1 VA7 audio circuit.

## Controller connections

Unchanged from O1; see its [connection table](../dual-db9-opt-pcb/README.md#connections-from-the-genthang-constraints-file).
Player 1 is entirely on J6 and player 2 entirely on J5. Pin 5 of each DB9 is 3.3 V.

## Firmware

Use the standard DB9 build from the official
[GenThang v1.9.3 release](https://github.com/shawnchivers/genthang/releases/tag/v1.9.3),
with **`audio_jack_l` on GPIO31 and `audio_jack_r` on GPIO17**.
Download [genthang_nano20k_db9_flash.bin](https://github.com/shawnchivers/genthang/releases/download/v1.9.3/genthang_nano20k_db9_flash.bin)
and its [checksums](https://github.com/shawnchivers/genthang/releases/download/v1.9.3/SHA256SUMS).
Program the complete flash image at address **0x000000**; it includes the matching
1.9.3 menu firmware and replaces the provisional GPIO17 package.
Released images through 1.9.2 output right audio on GPIO56 and do not match L3.
The generator reads the pin assignments, including the two audio pins, from
`genthang/src/boards/nano20k_db9.cst`; a copy is in
[reference/built-pinout.cst](reference/built-pinout.cst), and the check fails if the
board, schematic and constraints disagree.
When this design is imported under GenThang's `hardware/` directory, the generator
reads that repository's `src/boards/nano20k_db9.cst` directly.

L1/L2 compatibility: with the Tang removed from the carrier, an isolated jumper
from **Tang J6.15 to PCB J5.7** can feed the old right filter from the new firmware.
Do not also connect Tang J5.7 (GPIO56) to that filter. Power off before rewiring.

## Files

- [Routed KiCad PCB](dual-db9-lineout-pcb.kicad_pcb), [schematic PDF](schematic.pdf)
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
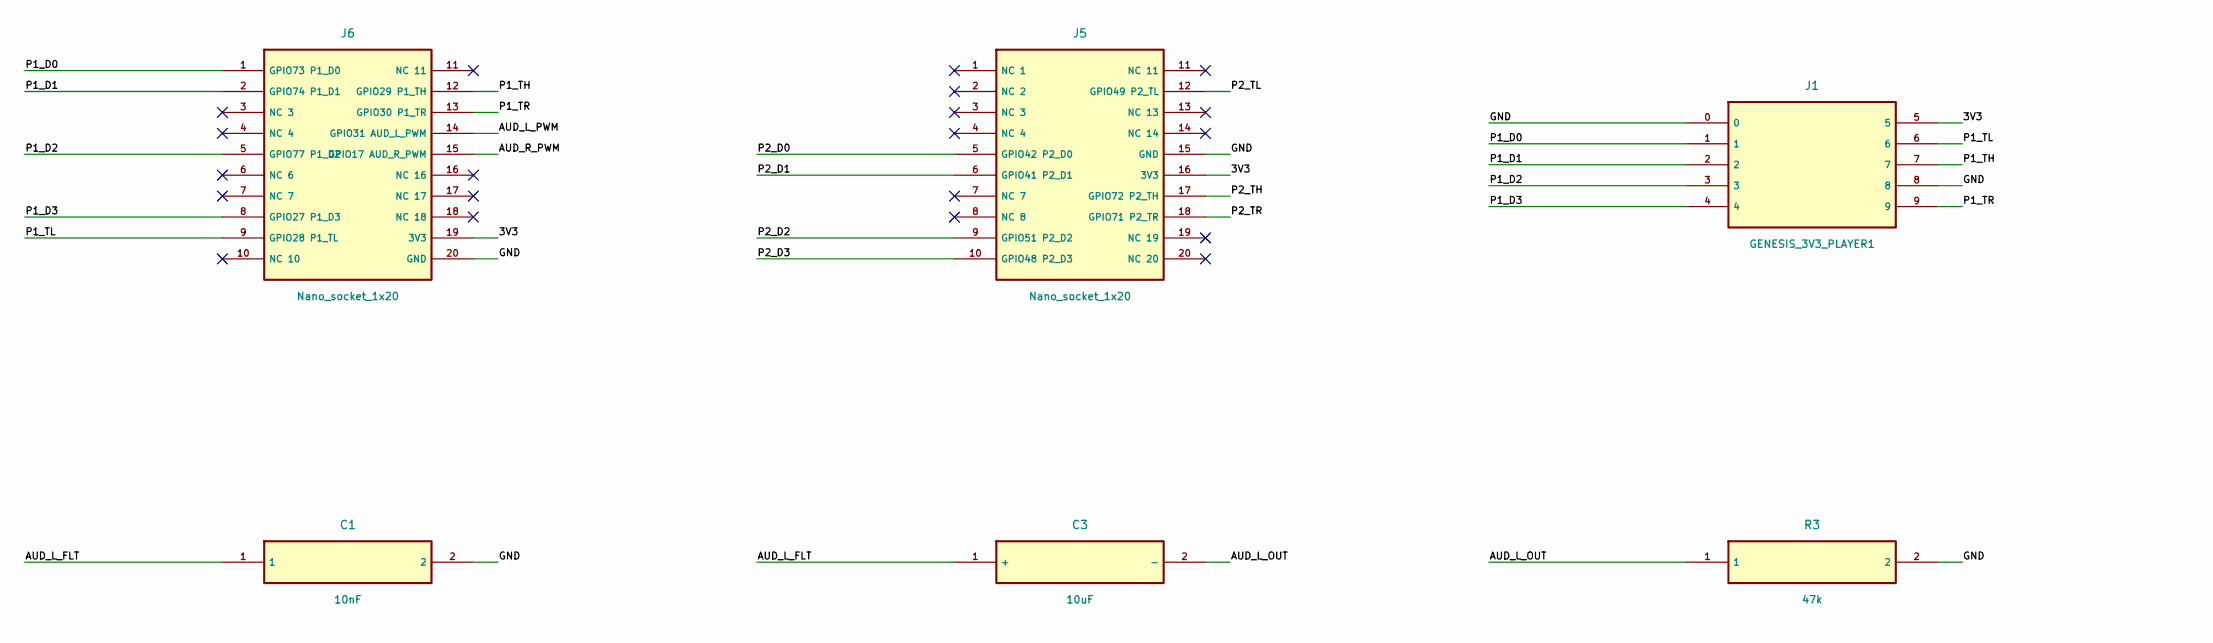
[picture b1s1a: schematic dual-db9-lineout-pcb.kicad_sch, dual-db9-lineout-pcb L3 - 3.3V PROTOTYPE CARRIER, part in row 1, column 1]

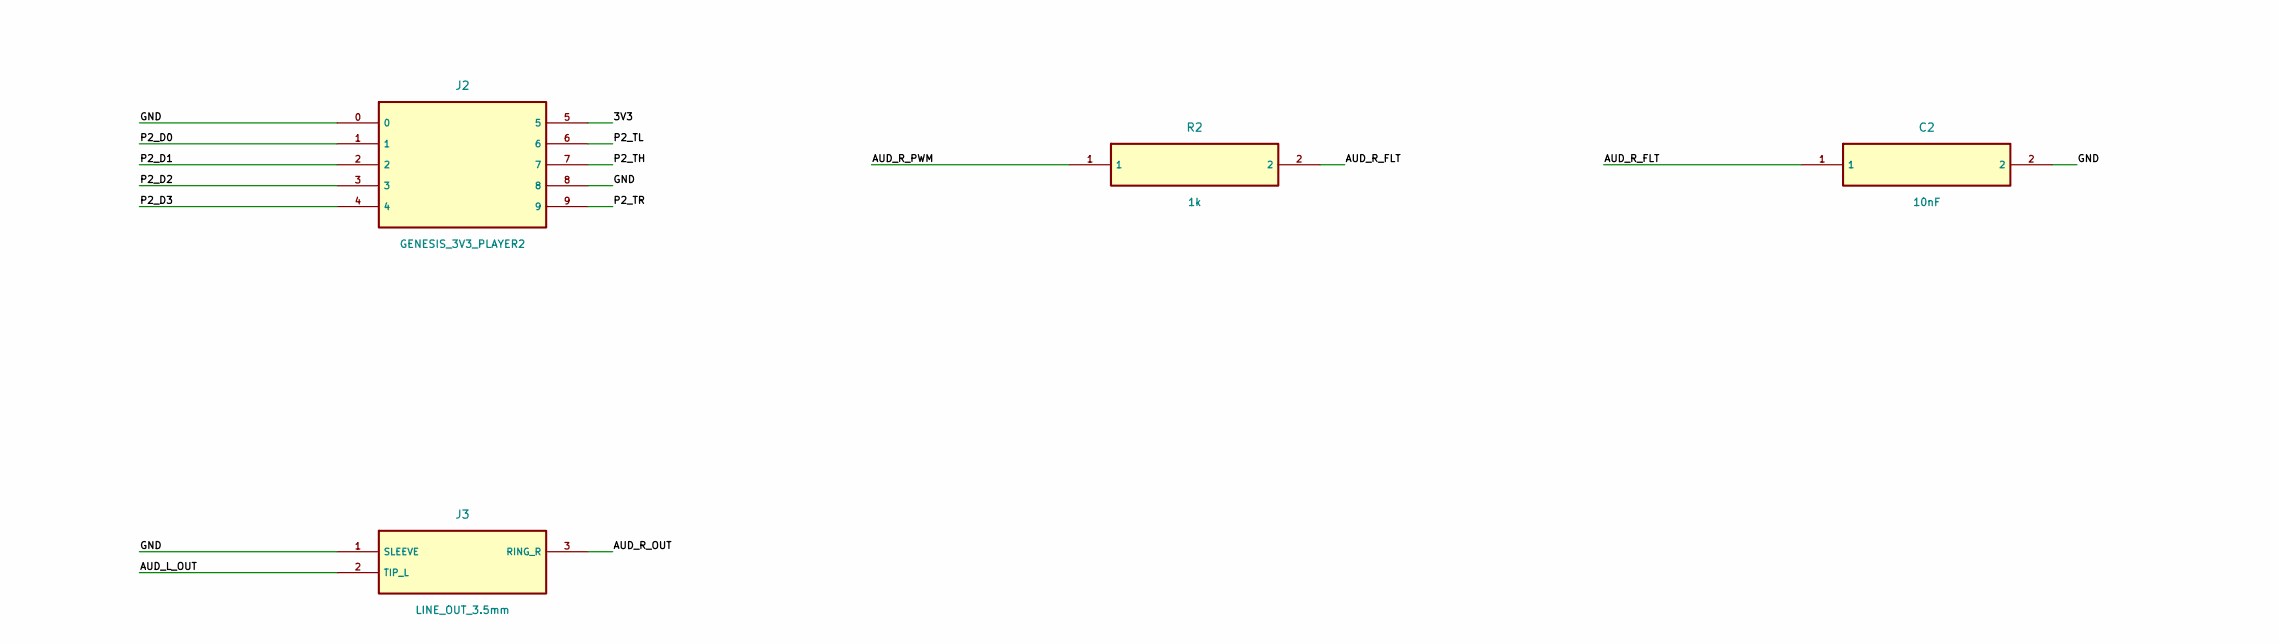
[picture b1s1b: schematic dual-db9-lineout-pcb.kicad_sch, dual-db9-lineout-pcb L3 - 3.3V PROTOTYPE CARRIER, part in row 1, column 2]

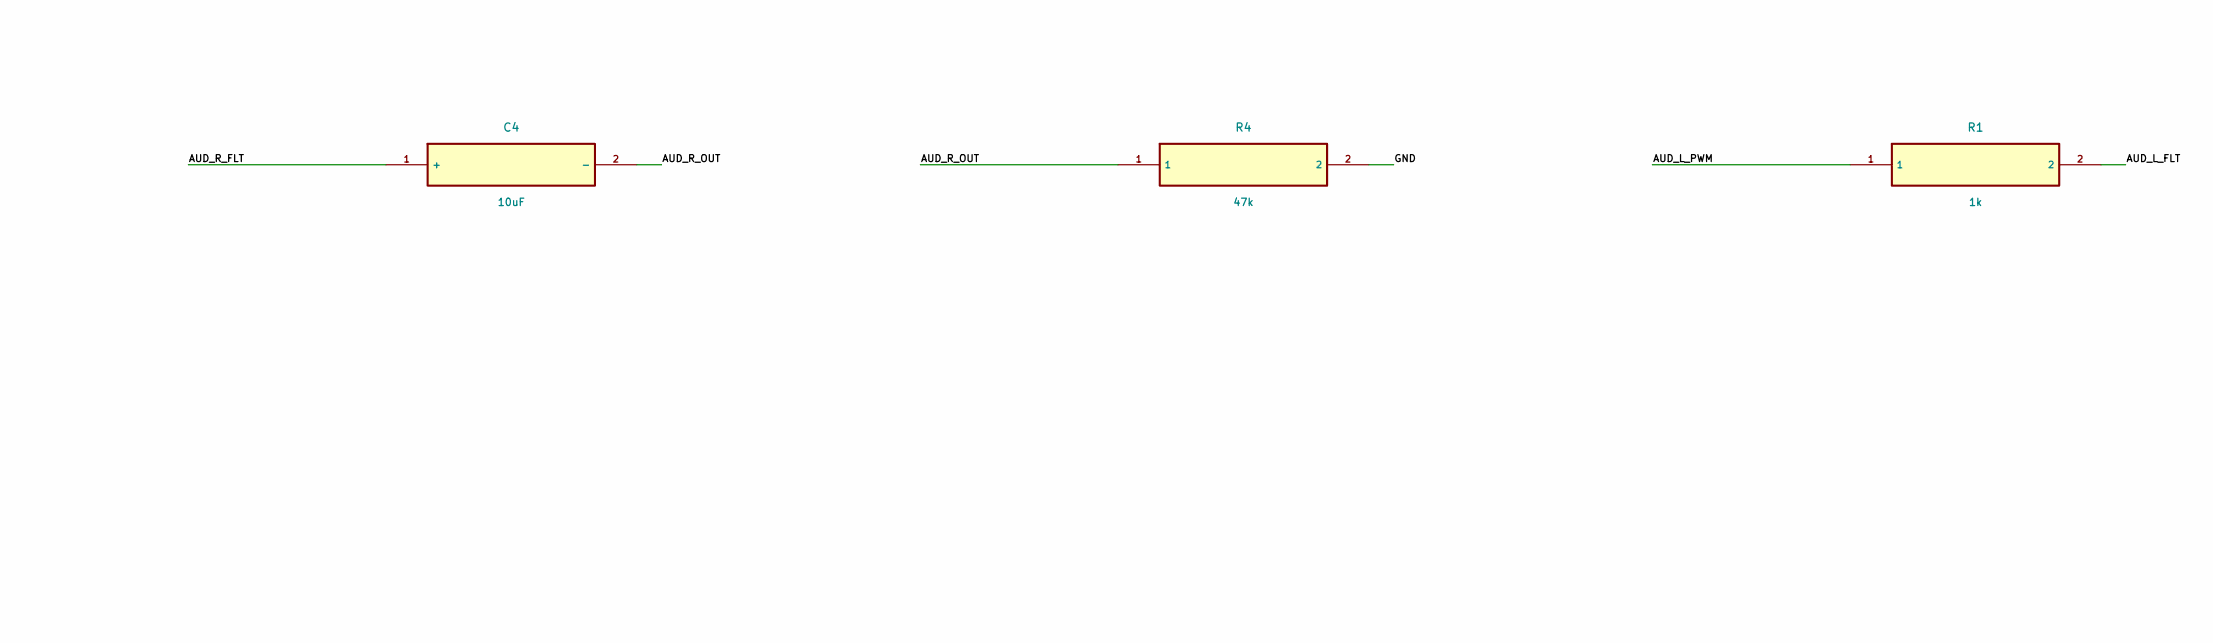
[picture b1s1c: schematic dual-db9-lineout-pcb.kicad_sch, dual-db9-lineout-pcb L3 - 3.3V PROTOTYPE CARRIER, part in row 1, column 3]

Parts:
C1, C2: 10nF; C_Disc_D5.0mm_W2.5mm_P5.00mm
C3, C4: 10uF; CP_Radial_D5.0mm_P2.00mm
J1: GENESIS_3V3_PLAYER1; Kycon_K22X-E9P-N
J2: GENESIS_3V3_PLAYER2; Kycon_K22X-E9P-N
J3: LINE_OUT_3.5mm; Jack_3.5mm_CUI_SJ1-3523N_Horizontal
J5, J6: Nano_socket_1x20; Harwin_M20-7822046_1x20
R1, R2: 1k; R_Axial_DIN0207_L6.3mm_D2.5mm_P7.62mm_Horizontal
R3, R4: 47k; R_Axial_DIN0207_L6.3mm_D2.5mm_P7.62mm_Horizontal

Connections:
3V3: J1.5, J2.5, J5.16 (3V3), J6.19 (3V3)
AUD_L_FLT: C1.1, C3.1 (+), R1.2
AUD_L_OUT: C3.2 (-), J3.2 (TIP_L), R3.1
AUD_L_PWM: J6.14 (GPIO31 AUD_L_PWM), R1.1
AUD_R_FLT: C2.1, C4.1 (+), R2.2
AUD_R_OUT: C4.2 (-), J3.3 (RING_R), R4.1
AUD_R_PWM: J6.15 (GPIO17 AUD_R_PWM), R2.1
GND: C1.2, C2.2, J1.0, J1.8, J2.0, J2.8, J3.1 (SLEEVE), J5.15 (GND), J6.20 (GND), R3.2, R4.2
P1_D0: J1.1, J6.1 (GPIO73 P1_D0)
P1_D1: J1.2, J6.2 (GPIO74 P1_D1)
P1_D2: J1.3, J6.5 (GPIO77 P1_D2)
P1_D3: J1.4, J6.8 (GPIO27 P1_D3)
P1_TH: J1.7, J6.12 (GPIO29 P1_TH)
P1_TL: J1.6, J6.9 (GPIO28 P1_TL)
P1_TR: J1.9, J6.13 (GPIO30 P1_TR)
P2_D0: J2.1, J5.5 (GPIO42 P2_D0)
P2_D1: J2.2, J5.6 (GPIO41 P2_D1)
P2_D2: J2.3, J5.9 (GPIO51 P2_D2)
P2_D3: J2.4, J5.10 (GPIO48 P2_D3)
P2_TH: J2.7, J5.17 (GPIO72 P2_TH)
P2_TL: J2.6, J5.12 (GPIO49 P2_TL)
P2_TR: J2.9, J5.18 (GPIO71 P2_TR)

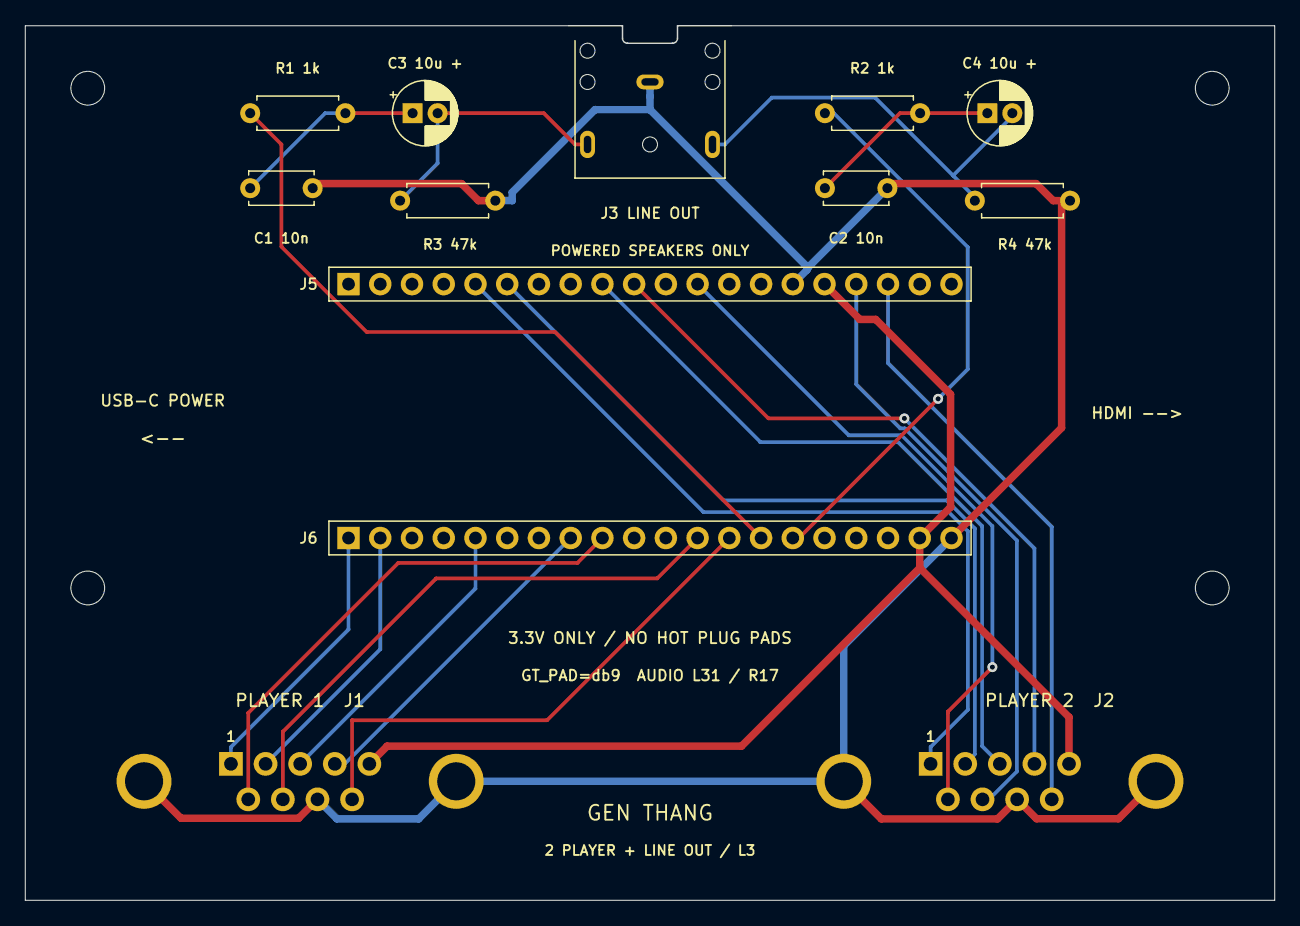
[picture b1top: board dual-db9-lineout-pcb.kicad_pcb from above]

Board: 2 copper layers, 100.0 x 70.0 mm, 17 parts (0 on the bottom side), 22 nets.

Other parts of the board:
H1, H2, H3, H4: M2.5_clearance; Mount_M2_5

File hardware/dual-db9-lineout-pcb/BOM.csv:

Line,Quantity Per Board,Reference Designator,Manufacturer,Manufacturer Part Number,Description,Package,Type,Substitutions,Source URL
1,2,J5 J6,Harwin,M20-7822046,1x20 female socket; 2.54mm pitch; 8.5mm body height,1x20 SIL,Through-hole,Any 1x20 2.54 mm female header of similar height,https://www.harwin.com/products/M20-7822046
2,2,J1 J2,Kycon,K22X-E9P-N,Male DE9 right angle; boardlocks; recessed 4-40 inserts; NOT NJ,DE9 right angle THT,Through-hole,NO - fit of other DB9 parts is not verified,https://www.kycon.com/Pub_Eng_Draw/K22X-E9P-N.pdf
3,1,J3,CUI / Same Sky,SJ1-3523N,"3.5 mm stereo jack, right angle, 3 conductor",THT slotted pins,Through-hole,Must match SJ1-3523N footprint,https://www.cuidevices.com/product/resource/pdf/sj1-352xn.pdf
4,2,R1 R2,Any,1 kOhm,"1 kOhm 1/4 W axial, 7.62 mm (0.3 in) pitch",Axial DIN0207,Through-hole,Yes,
5,2,R3 R4,Any,47 kOhm,"47 kOhm 1/4 W axial, 7.62 mm pitch; 22k-100k fine",Axial DIN0207,Through-hole,Yes,
6,2,C1 C2,Any,10 nF (103),"10 nF 50 V ceramic disc, 5.0 mm pitch",Disc 5.0 mm pitch,Through-hole,Yes; film capacitor of same pitch also fine,
7,2,C3 C4,Any,10 uF,"10 uF 25 V radial electrolytic, 5 mm dia, 2.0 mm pitch; POLARIZED",Radial 5 mm dia 2.0 mm pitch,Through-hole,Yes; 2.5 mm pitch leads can be bent,

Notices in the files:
README.md:
Gen Thang is distributed under the [GNU General Public License v3](LICENSE).
Bundled third-party components keep their own licences and notices; see
[THIRD_PARTY.md](THIRD_PARTY.md).
kind (see the GPL). You are responsible for using only ROMs you are legally entitled
